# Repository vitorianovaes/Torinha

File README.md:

<h1 align="center">
    📡 Projeto da Torinha 😼

<h3>Tabela de conteúdos</h3>
    
=================
<!--ts-->
   * [Sobre o projeto](#-sobre-o-projeto)
   * [Funcionalidades](#-funcionalidades)
   * [Como executar o projeto](#-como-executar-o-projeto)
     * [Pré-requisitos](#pré-requisitos)

## 💻 Sobre o projeto

📡 Esse projeto de circuito de comunicação wireless foi desenvolvido para o desafio da Tractian; Tem como objetivo enviar um arquivo de 500kb a partir de um espaço aberto de 100m usando uma bateria. 
  
## ⚙️ Componentes 
  
_Placa de Transmissão:_
    <!--ts-->
   * Transmissor RF 433 mhz: foi escolhido porque é fácil de encontrar em lojas, é barato e opera entre 0m-150m;
   * Bateria; <br>
   * ATMEGA 328P: foi escolhido pela praticidade e custo benefício. O ATMEGA é pequeno em relação ao Arduíno, economizando espaço e portas, apesar de usarem a mesma tecnologia; <br>
   * Resistor: para o LED e bateria;
   * Cartão SD: foi escolhido pela facilidade de operação; <br>
   * Botão de enviar (Push Button); <br>
   * Botão de Liga/Desliga (Switch); <br>
   * LED 5mm: para mostrar ao usuário que o arquivo foi enviado corretamente; <br>
  
  _Placa de Recepção:_
   * Receptor RF 433 mhz; <br>
   * Bateria; <br>
   * ATMEGA 328P; <br>
   * Resistor; <br>
   * Cartão SD; <br>
   * LED; <br>
   * Botão Liga/Desliga; <br>

## ⚙️ Funcionalidades

- [x] Consegue enviar um arquivo 500kb entre 0m-150m;

## 🚀 Como executar o projeto

Este projeto é divido em duas partes:
1. Hardware
2. Firmware <br>
    
    Hardware: schematic e PCB; <br>
    Firmware: a lógica do código fonte é colocar um SD card contendo o arquivo (nomeado BOB.txt) a ser mandado via rádio frequência. O microcontrolador lê o arquivo e o usuário ao pressionar o Push Button inicia o envio do arquivo. Se o arquivo for enviado corretamente o LED irá piscar três vezes. Para se certificar de que todo o arquivo foi enviado, o buffer é limpo e um sinal de Carriage Return (\r) é enviado para o Receptor, onde o LED vai piscar três vezes para confirmar o recebimento do arquivo.

### Pré-requisitos

Antes de começar, você vai precisar ter instalado em sua máquina a seguinte ferramenta:
[Eagle](https://www.autodesk.com/products/eagle/free-download).
Além disto é bom ter um editor para trabalhar com o código como [VSCode](https://code.visualstudio.com/)

Feito com ❤️ por Torinha 😼

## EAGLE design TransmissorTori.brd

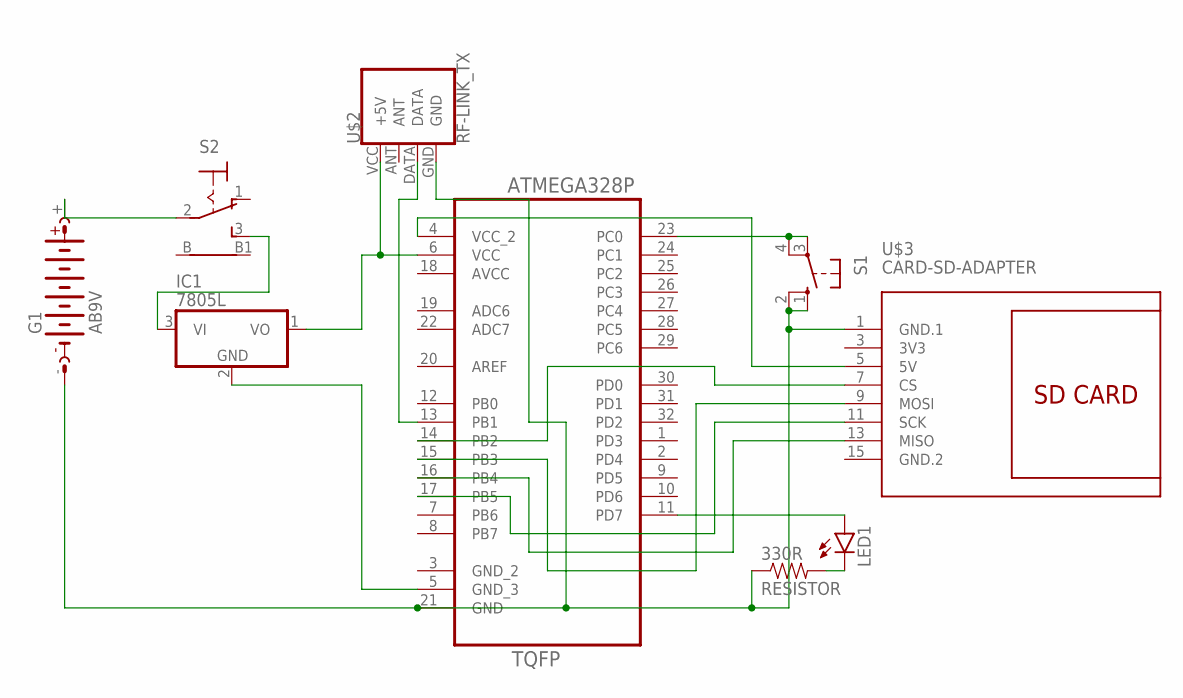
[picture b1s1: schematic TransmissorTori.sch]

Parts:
330R: RESISTOR; 0603RES
G1: AB9V
IC1: 7805L; TO92
LED1: LED5MM
S1: 10-XX; B3F-10XX
S2: 9070-1W
U1: ATMEGA328P-AU; QFP80P900X900X120-32N
U$2: RF-LINK_TX
U$3: CARD-SD-ADAPTER

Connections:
3V3: U$3.3 (3V3)
AVCC: U1.18 (AVCC)
GND.2: U$3.15 (GND.2)
unnamed: G1.+, S2.2
unnamed: IC1.1 (VO), U1.6 (VCC), U$2.VCC (+5V)
unnamed: 330R.1, G1.-, S1.1 (S), S1.2 (S1), U1.21 (GND), U$2.GND, U$3.1 (GND.1)
unnamed: U1.15 (PB3), U$3.9 (MOSI)
unnamed: U1.17 (PB5), U$3.11 (SCK)
unnamed: U1.16 (PB4), U$3.13 (MISO)
unnamed: U1.14 (PB2), U$3.7 (CS)
unnamed: U1.4 (VCC_2), U$3.5 (5V)
unnamed: U1.13 (PB1), U$2.DATA
unnamed: IC1.2 (GND), U1.5 (GND_3)
unnamed: IC1.3 (VI), S2.3 (S)
unnamed: 330R.2, LED1.K (C)
unnamed: LED1.A, U1.11 (PD7)
unnamed: S1.3, S1.4 (P1), U1.23 (PC0)

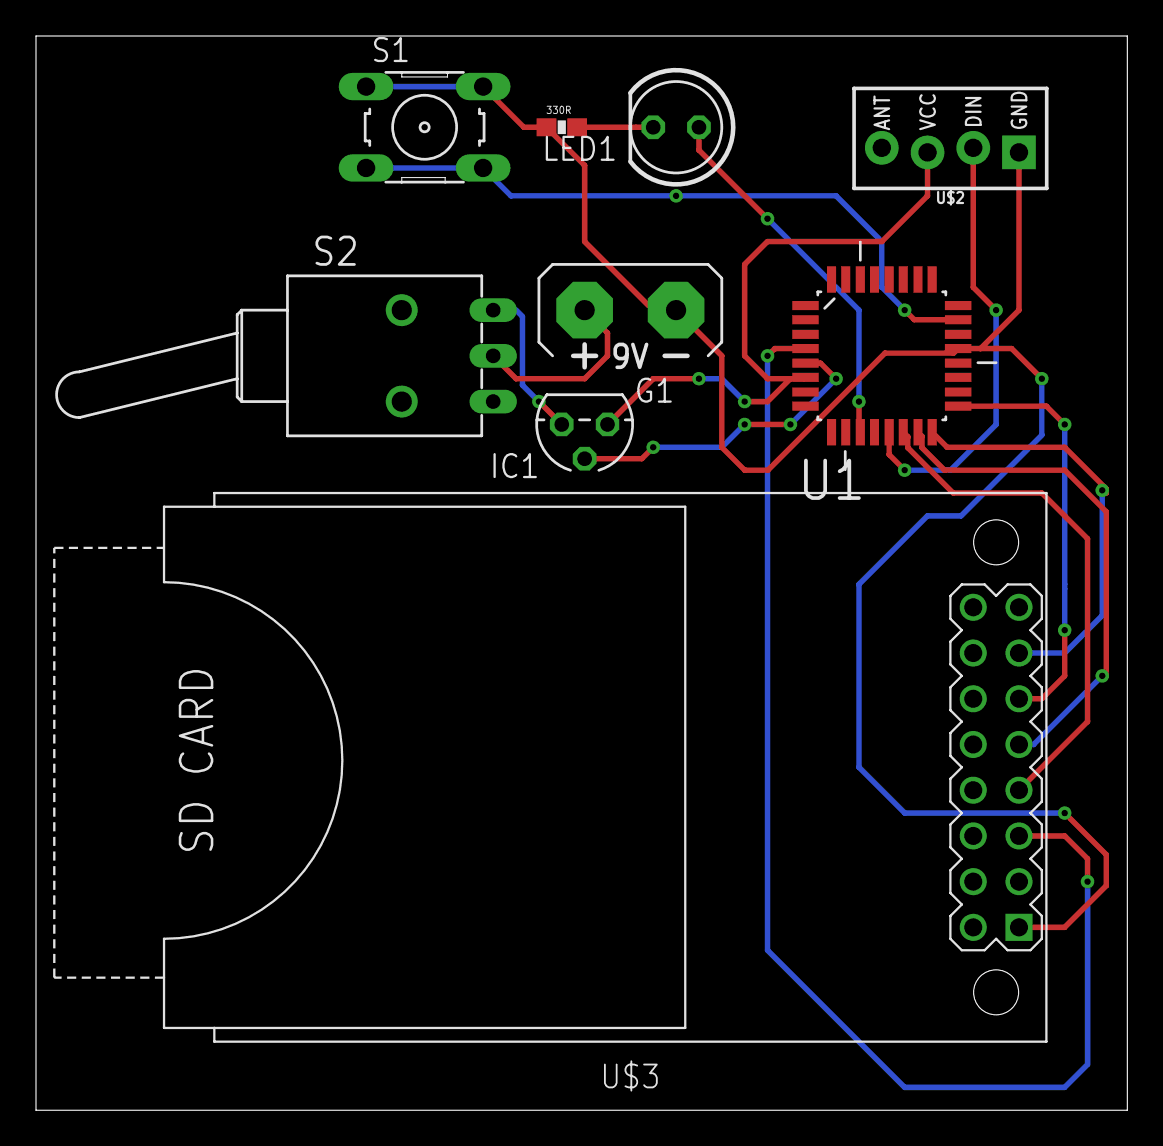
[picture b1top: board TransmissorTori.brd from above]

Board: 2 copper layers, 60.6 x 59.7 mm, 9 parts (0 on the bottom side), 14 nets.

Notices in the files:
parts and their libraries:
SparkFun-RF: Licensing: Creative Commons ShareAlike 4.0 International - https://creativecommons.org/licenses/by-sa/4.0
diy-modules: Released under the Creative Commons Attribution 4.0 International License: http://creativecommons.org/licenses/by/4.0
